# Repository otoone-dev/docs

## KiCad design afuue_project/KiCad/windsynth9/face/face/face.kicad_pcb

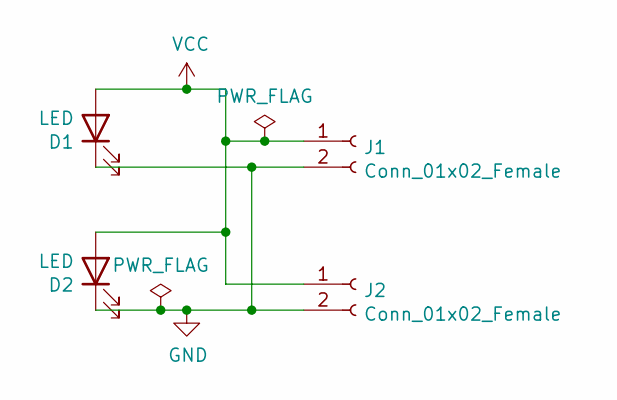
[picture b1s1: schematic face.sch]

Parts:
D1, D2: LED; LED_0603_1608Metric
J1, J2: Conn_01x02_Female; ContactPad_4mm

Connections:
GND: D1.1 (K), D2.1 (K), J1.2, J2.2
VCC: D1.2 (A), D2.2 (A), J1.1, J2.1

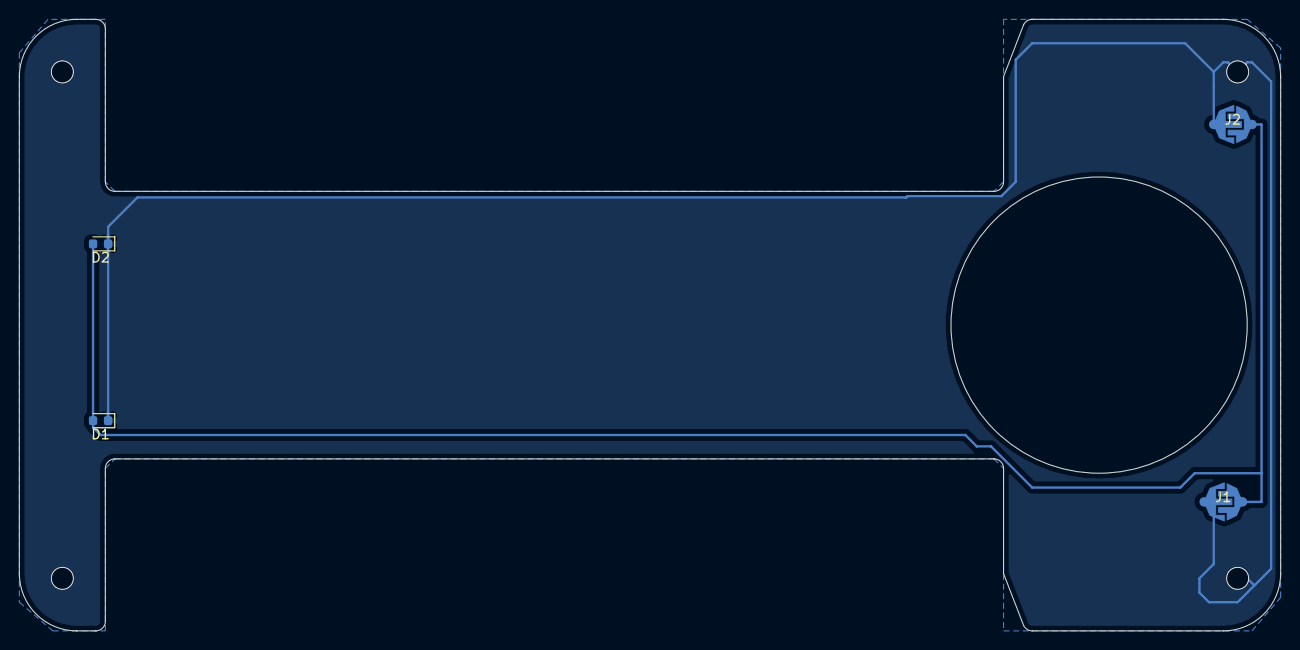
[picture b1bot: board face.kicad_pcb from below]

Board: 2 copper layers, 132.0 x 64.0 mm, 4 parts (4 on the bottom side), 2 nets.

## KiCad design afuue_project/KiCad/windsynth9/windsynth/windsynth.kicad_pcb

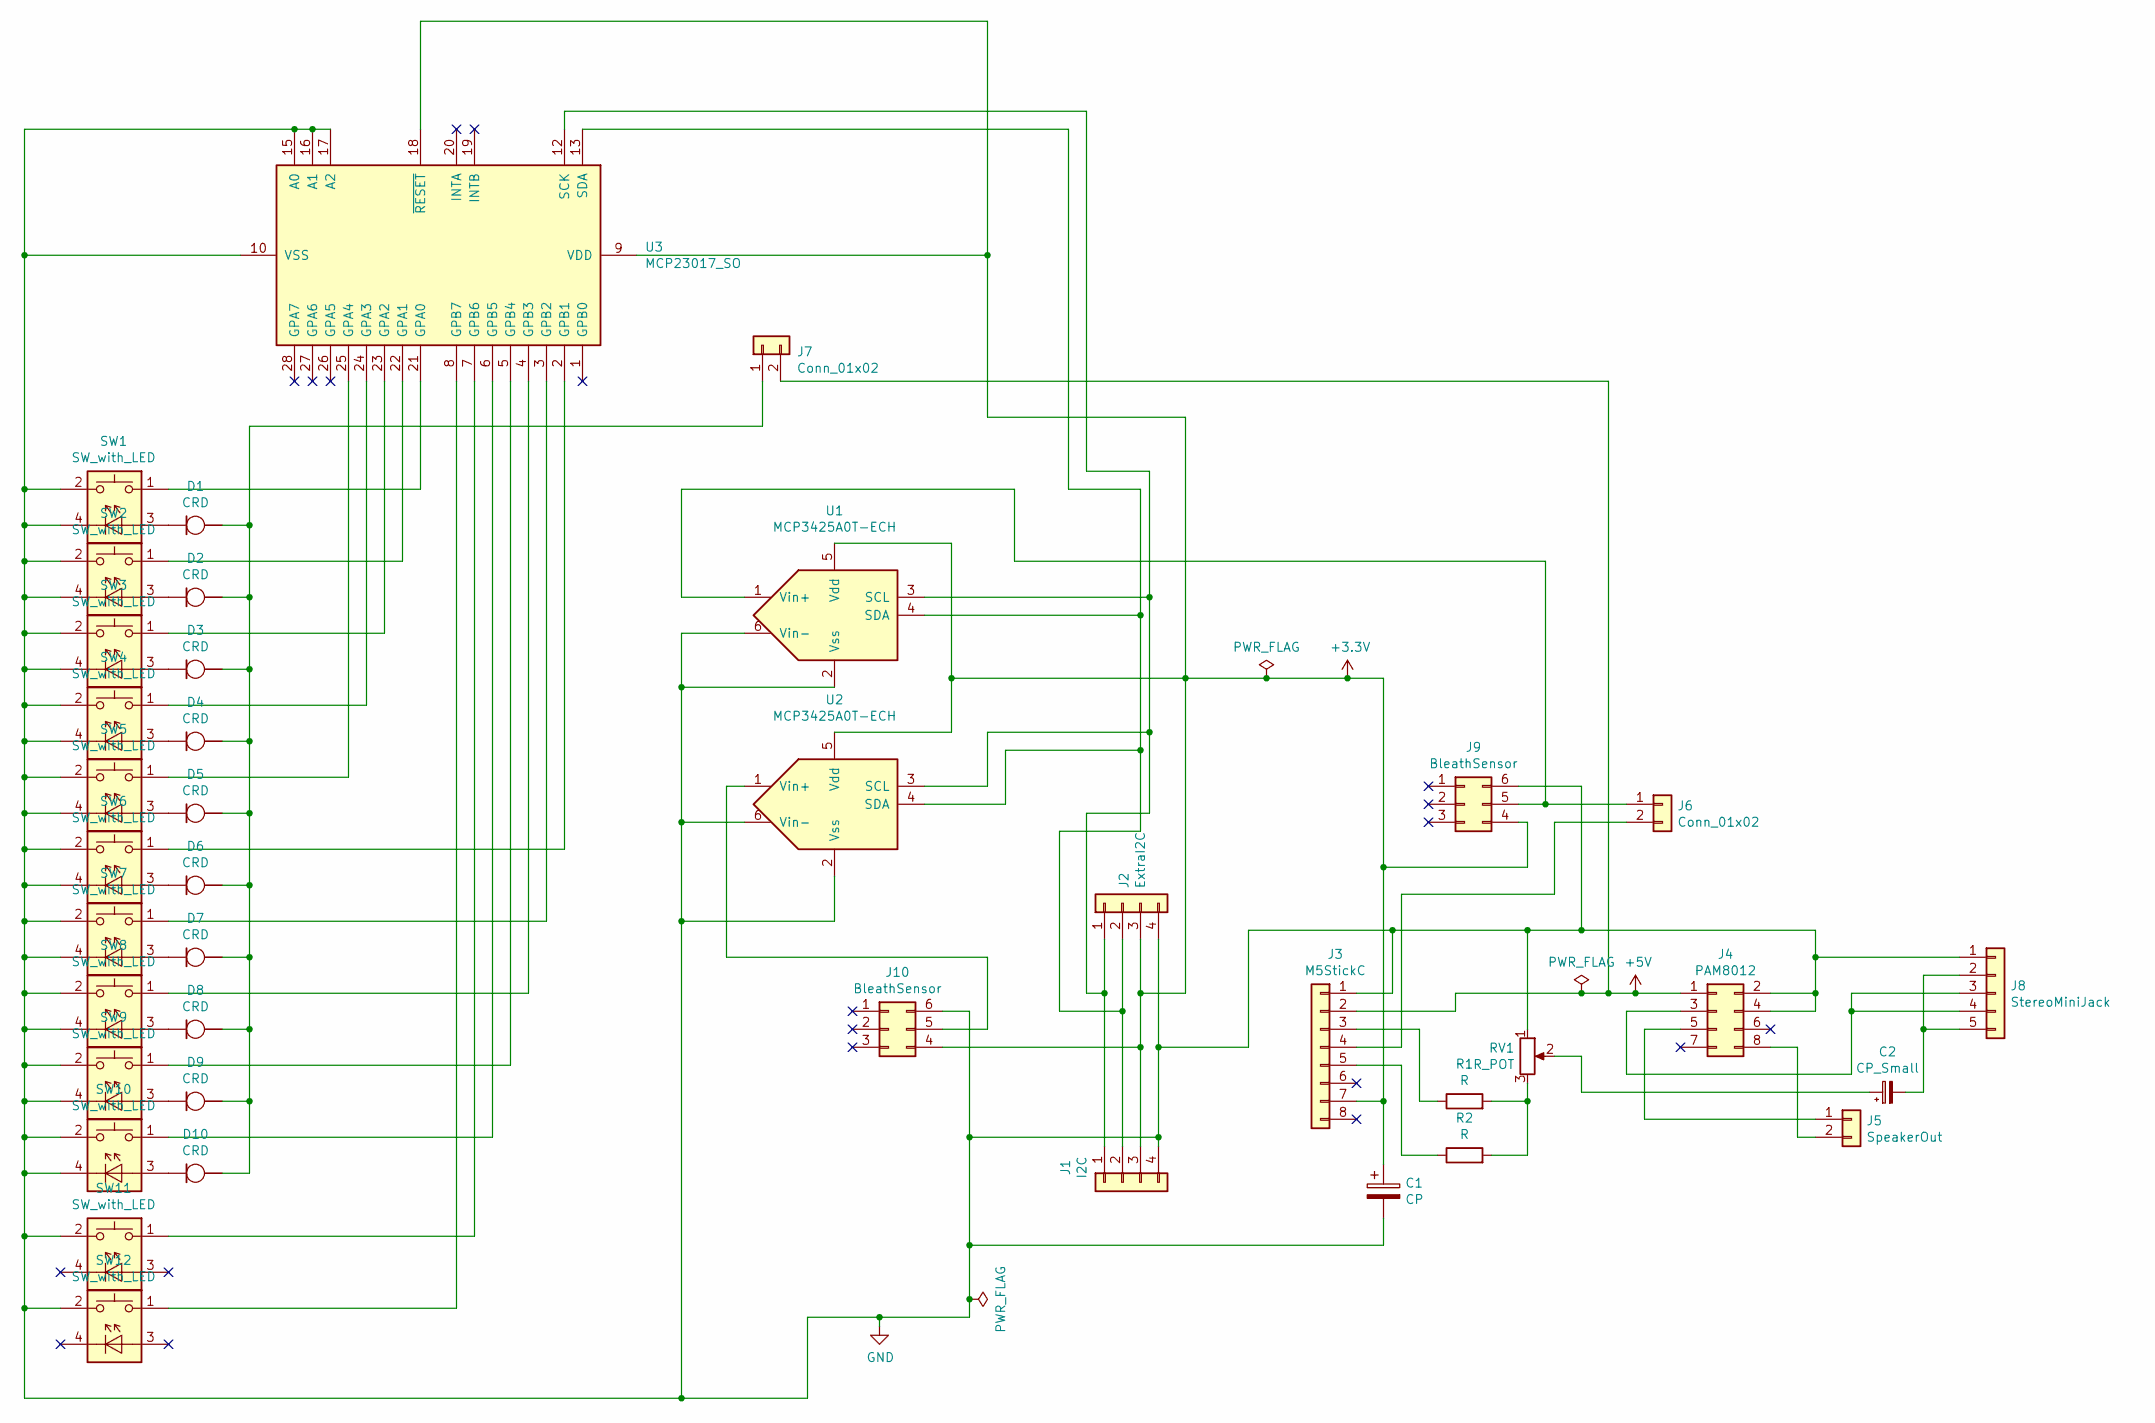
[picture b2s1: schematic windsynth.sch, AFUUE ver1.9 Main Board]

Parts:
C1: CP; PinHeader_1x02_P2.54mm_Vertical
C2: CP_Small; PinHeader_1x02_P2.54mm_Vertical
D1, D2, D3, D4, D5, D6, D7, D8, D9, D10: CRD; LED_0805_2012Metric
J1: I2C; JST_PH_B4B-PH-SM4-TB_1x04-1MP_P2.00mm_Vertical
J2: ExtraI2C; PinHeader_1x04_P2.00mm_Vertical
J3: M5StickC; PinHeader_1x08_P2.54mm_Horizontal
J4: PAM8012; AE-PAM8012
J5: SpeakerOut; USGM30
J6, J7: Conn_01x02; SolderJumper-2_P1.3mm_Open_RoundedPad1.0x1.5mm
J8: StereoMiniJack; PJ-307 AudioJack
J9, J10: BleathSensor; DIP-6_W7.62mm_Reverse
R1, R2: R; PinHeader_1x02_P2.54mm_Vertical
RV1: R_POT; R1001-N16
SW1, SW2, SW3, SW4, SW5, SW6, SW7, SW8, SW9, SW10, SW11, SW12: SW_with_LED; KailhLowProfileSW
U1, U2: MCP3425A0T-ECH; SOT-23-6_Handsoldering
U3: MCP23017_SO; SOIC-28W_7.5x17.9mm_P1.27mm

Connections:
GND: C1.2, J1.4, J2.4, J3.1, J4.2, J4.4, J8.1, J9.6, J10.6, RV1.1, SW1.2, SW1.4, SW2.2, SW2.4, SW3.2, SW3.4, SW4.2, SW4.4, SW5.2, SW5.4, SW6.2, SW6.4, SW7.2, SW7.4, SW8.2, SW8.4, SW9.2, SW9.4, SW10.2, SW10.4, SW11.2, SW12.2, U1.2 (Vss), U1.6 (Vin-), U2.2 (Vss), U2.6 (Vin-), U3.10 (VSS), U3.15 (A0), U3.16 (A1), U3.17 (A2)
unnamed: C2.1, RV1.2
unnamed: C2.2, J8.2, J8.5
unnamed: D1.1 (K), SW1.3
unnamed: D1.2 (A), D2.2 (A), D3.2 (A), D4.2 (A), D5.2 (A), D6.2 (A), D7.2 (A), D8.2 (A), D9.2 (A), D10.2 (A), J7.1
unnamed: D2.1 (K), SW2.3
unnamed: D3.1 (K), SW3.3
unnamed: D4.1 (K), SW4.3
unnamed: D5.1 (K), SW5.3
unnamed: D6.1 (K), SW6.3
unnamed: D7.1 (K), SW7.3
unnamed: D8.1 (K), SW8.3
unnamed: D9.1 (K), SW9.3
unnamed: D10.1 (K), SW10.3
unnamed: J1.1, J2.1, U1.3 (SCL), U2.3 (SCL), U3.12 (SCK)
unnamed: J1.2, J2.2, U1.4 (SDA), U2.4 (SDA), U3.13 (SDA)
unnamed: J3.3, R1.1
unnamed 17: J3.4, J6.2; also elsewhere on the board
unnamed: J3.5, R2.1
unnamed: J4.3, J8.3, J8.4
unnamed: J4.5, J5.1
unnamed: J4.8, J5.2
unnamed 22: J6.1, J9.5, U1.1 (Vin+); also elsewhere on the board
unnamed: J10.5, U2.1 (Vin+)
unnamed: R1.2, R2.2, RV1.3
unnamed: SW1.1, U3.21 (GPA0)
unnamed: SW2.1, U3.22 (GPA1)
unnamed: SW3.1, U3.23 (GPA2)
unnamed: SW4.1, U3.24 (GPA3)
unnamed: SW5.1, U3.25 (GPA4)
unnamed: SW6.1, U3.2 (GPB1)
unnamed: SW7.1, U3.3 (GPB2)
unnamed: SW8.1, U3.4 (GPB3)
unnamed: SW9.1, U3.5 (GPB4)
unnamed: SW10.1, U3.6 (GPB5)
unnamed: SW11.1, U3.7 (GPB6)
unnamed: SW12.1, U3.8 (GPB7)

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
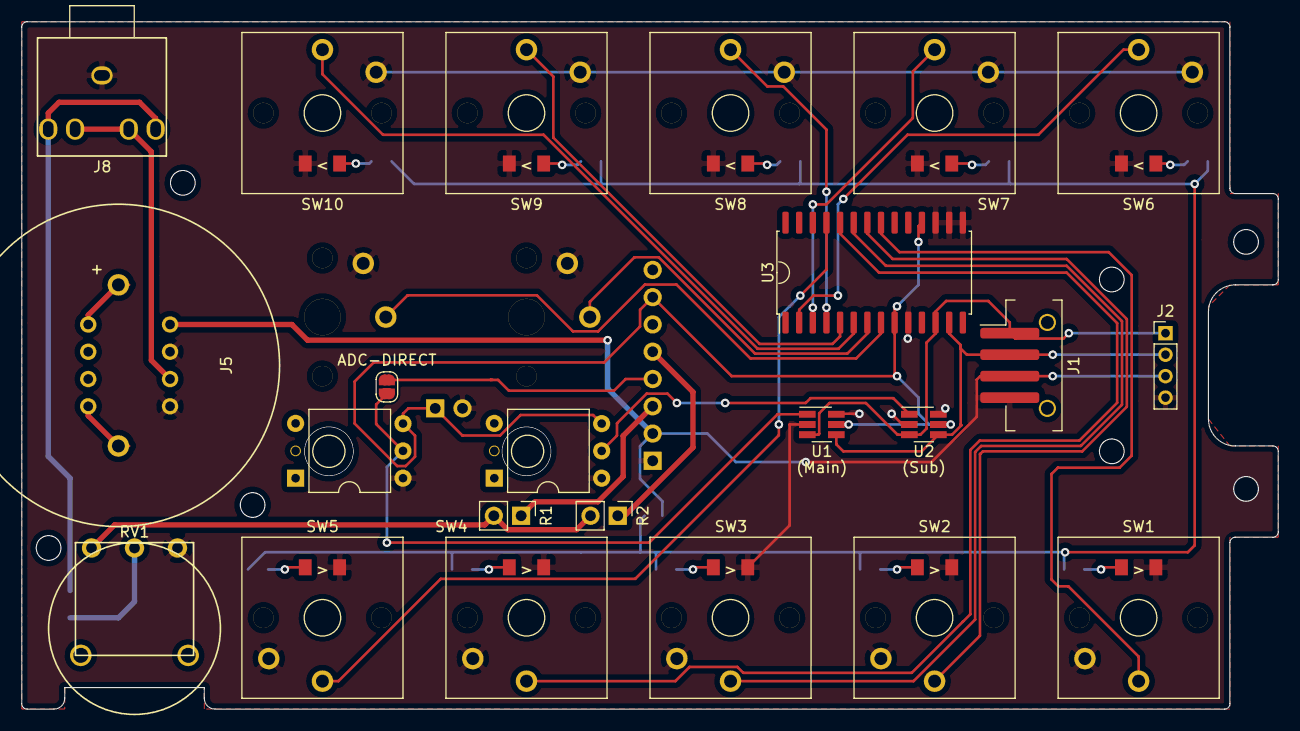
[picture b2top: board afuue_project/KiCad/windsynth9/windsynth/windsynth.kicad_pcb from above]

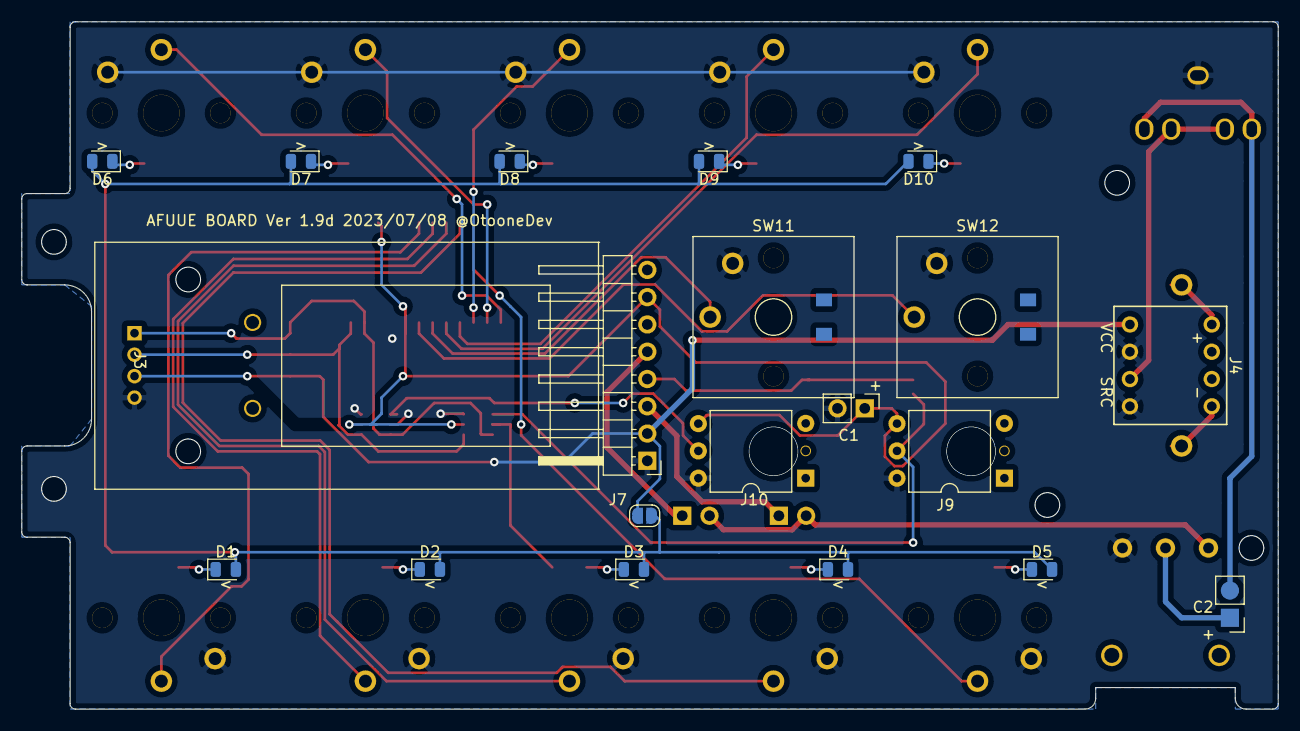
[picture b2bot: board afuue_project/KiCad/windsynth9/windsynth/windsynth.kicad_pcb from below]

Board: 2 copper layers, 117.0 x 64.0 mm, 40 parts (17 on the bottom side), 39 nets.

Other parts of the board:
ADC-DIRECT: Conn_01x02; SolderJumper-2_P1.3mm_Open_RoundedPad1.0x1.5mm

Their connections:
unnamed 17: ADC-DIRECT.2; also elsewhere on the board
unnamed 22: ADC-DIRECT.1; also elsewhere on the board

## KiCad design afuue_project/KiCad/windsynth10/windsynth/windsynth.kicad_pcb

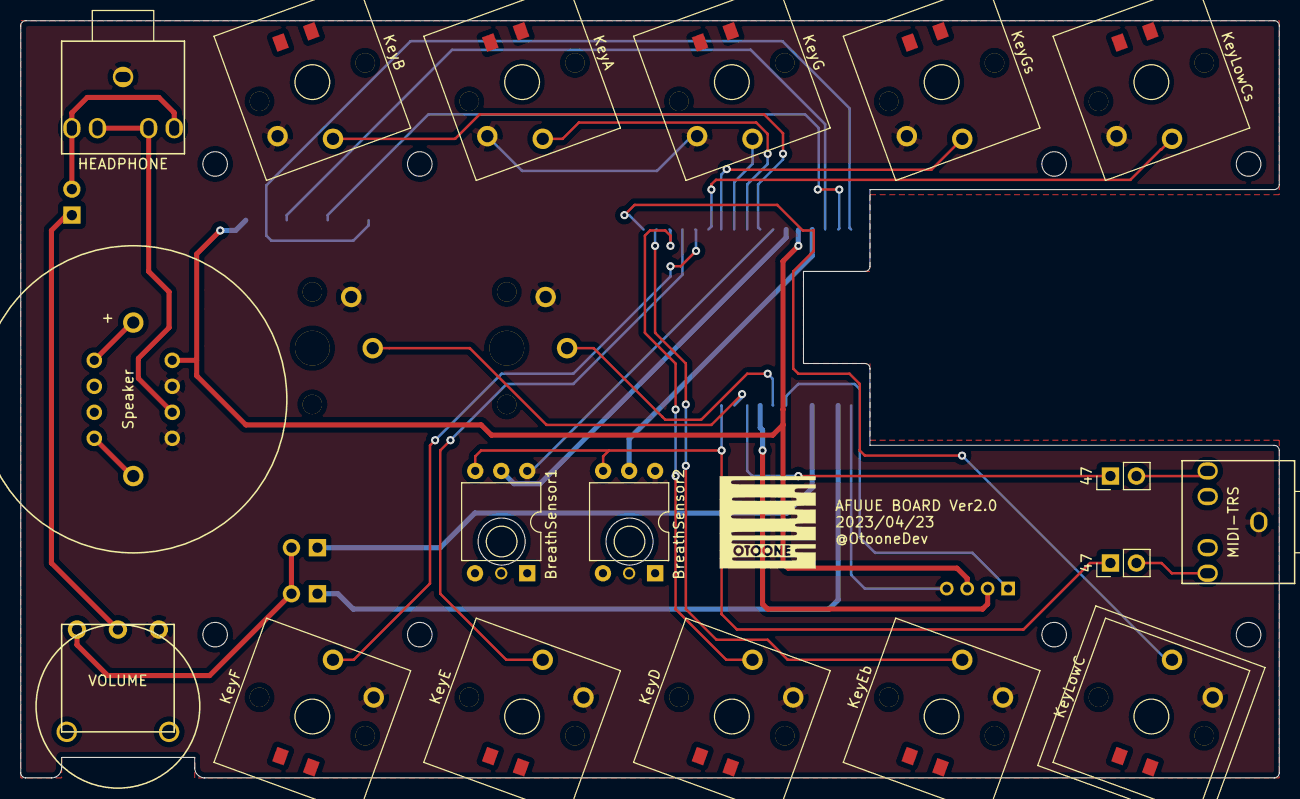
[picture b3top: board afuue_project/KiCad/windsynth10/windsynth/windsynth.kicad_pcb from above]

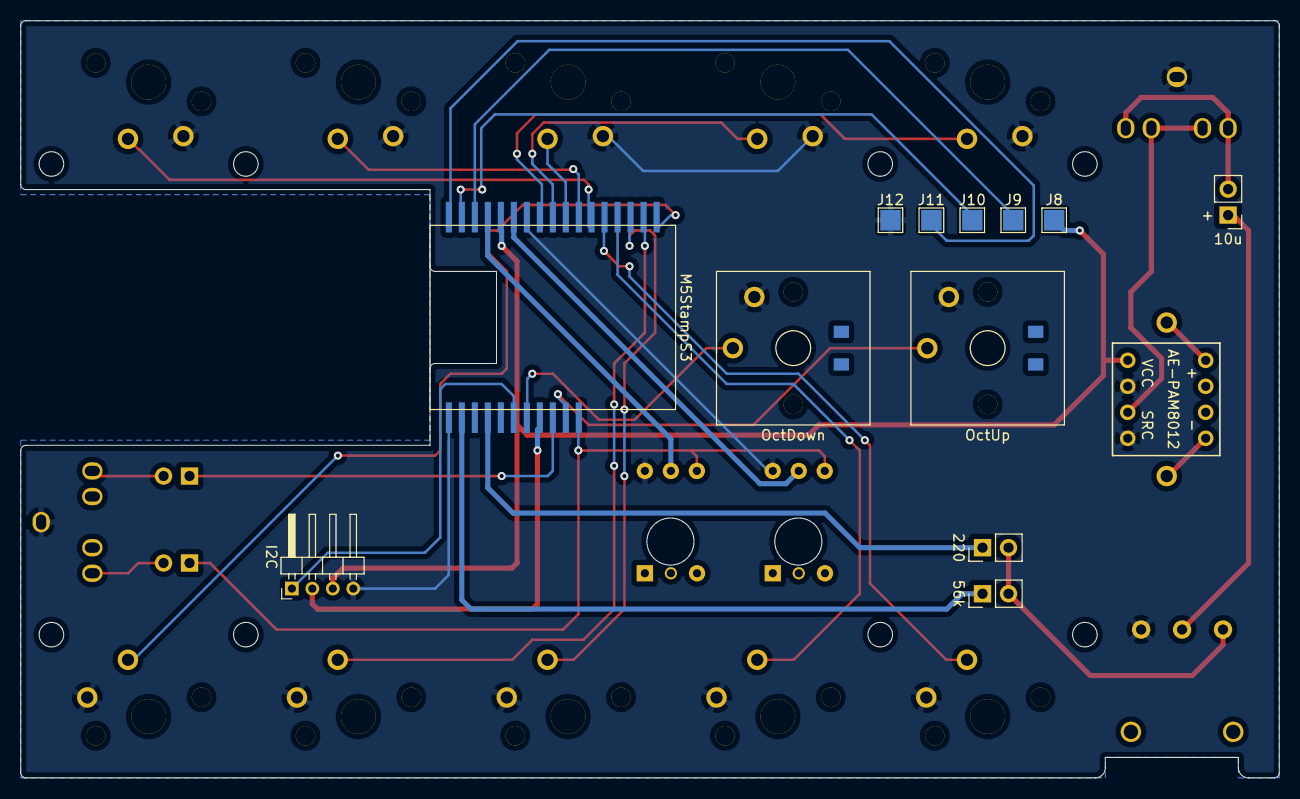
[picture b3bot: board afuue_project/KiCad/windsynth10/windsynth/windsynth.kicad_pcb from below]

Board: 2 copper layers, 123.0 x 74.0 mm, 31 parts (13 on the bottom side), 33 nets.

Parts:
10u: CP1_Small; PinHeader_1x02_P2.54mm_Vertical
47, 47#2: 47; PinHeader_1x02_P2.54mm_Vertical
56k: 56k; PinHeader_1x02_P2.54mm_Vertical
220: 220; PinHeader_1x02_P2.54mm_Vertical
AE-PAM8012: PAM8012; AE-PAM8012
BreathSensor1, BreathSensor2: BleathSensor; DIP-6_W7.62mm_Reverse
HEADPHONE: StereoMiniJack; PJ-307 AudioJack
I2C: I2C; PinHeader_1x04_P2.00mm_Horizontal
J8, J9, J10, J11, J12: Conn_01x01_Male; TestPoint_Pad_2.0x2.0mm
KeyA: SW_with_LED; KailhLowProfileSW
KeyB: SW_with_LED; KailhLowProfileSW
KeyD: SW_with_LED; KailhLowProfileSW
KeyE: SW_with_LED; KailhLowProfileSW
KeyEb: SW_with_LED; KailhLowProfileSW
KeyF: SW_with_LED; KailhLowProfileSW
KeyG: SW_with_LED; KailhLowProfileSW
KeyGs: SW_with_LED; KailhLowProfileSW
KeyLowC: SW_with_LED; KailhLowProfileSW
KeyLowCs: SW_with_LED; KailhLowProfileSW
M5StampS3: M5StampS3
MIDI-TRS: MIDI-TRS; PJ-307 AudioJack
OctDown: SW_with_LED; KailhLowProfileSW
OctUp: SW_with_LED; KailhLowProfileSW
Speaker: SpeakerOut; USGM30
VOLUME: R_POT; R1001-N16

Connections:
+3V3: 47#2.1, BreathSensor1.4, BreathSensor2.4, M5StampS3.28
+5V: AE-PAM8012.1, I2C.3, J8.1, M5StampS3.13
GND: AE-PAM8012.2, AE-PAM8012.4, BreathSensor1.6, BreathSensor2.6, HEADPHONE.1, I2C.4, J12.1, KeyA.2, KeyB.2, KeyD.2, KeyE.2, KeyEb.2, KeyF.2, KeyG.2, KeyGs.2, KeyLowC.2, KeyLowCs.2, M5StampS3.11, M5StampS3.18, MIDI-TRS.1, OctDown.2, OctUp.2, VOLUME.1
unnamed: 10u.1, VOLUME.2
unnamed: 10u.2, HEADPHONE.2, HEADPHONE.5
unnamed: BreathSensor1.5, M5StampS3.12
unnamed: BreathSensor2.5, M5StampS3.14
unnamed: AE-PAM8012.3, HEADPHONE.3, HEADPHONE.4
unnamed: 47.2, MIDI-TRS.2
unnamed: 47#2.2, MIDI-TRS.5
unnamed: AE-PAM8012.5, Speaker.1
unnamed: AE-PAM8012.8, Speaker.2
unnamed: I2C.1, M5StampS3.23
unnamed: I2C.2, M5StampS3.25
unnamed: J9.1, M5StampS3.15
unnamed: J10.1, M5StampS3.16
unnamed: J11.1, M5StampS3.17
unnamed: KeyA.1, M5StampS3.9
unnamed: KeyB.1, M5StampS3.10
unnamed: KeyD.1, M5StampS3.3
unnamed: KeyEb.1, M5StampS3.2
unnamed: KeyE.1, M5StampS3.4
unnamed: KeyF.1, M5StampS3.5
unnamed: KeyG.1, M5StampS3.8
unnamed: KeyGs.1, M5StampS3.7
unnamed: KeyLowC.1, M5StampS3.1
unnamed: KeyLowCs.1, M5StampS3.6
unnamed: M5StampS3.24, OctDown.1
unnamed: M5StampS3.27, OctUp.1
unnamed: 56k.1, M5StampS3.19
unnamed: 56k.2, 220.2, VOLUME.3
unnamed: 220.1, M5StampS3.21
unnamed: 47.1, M5StampS3.26

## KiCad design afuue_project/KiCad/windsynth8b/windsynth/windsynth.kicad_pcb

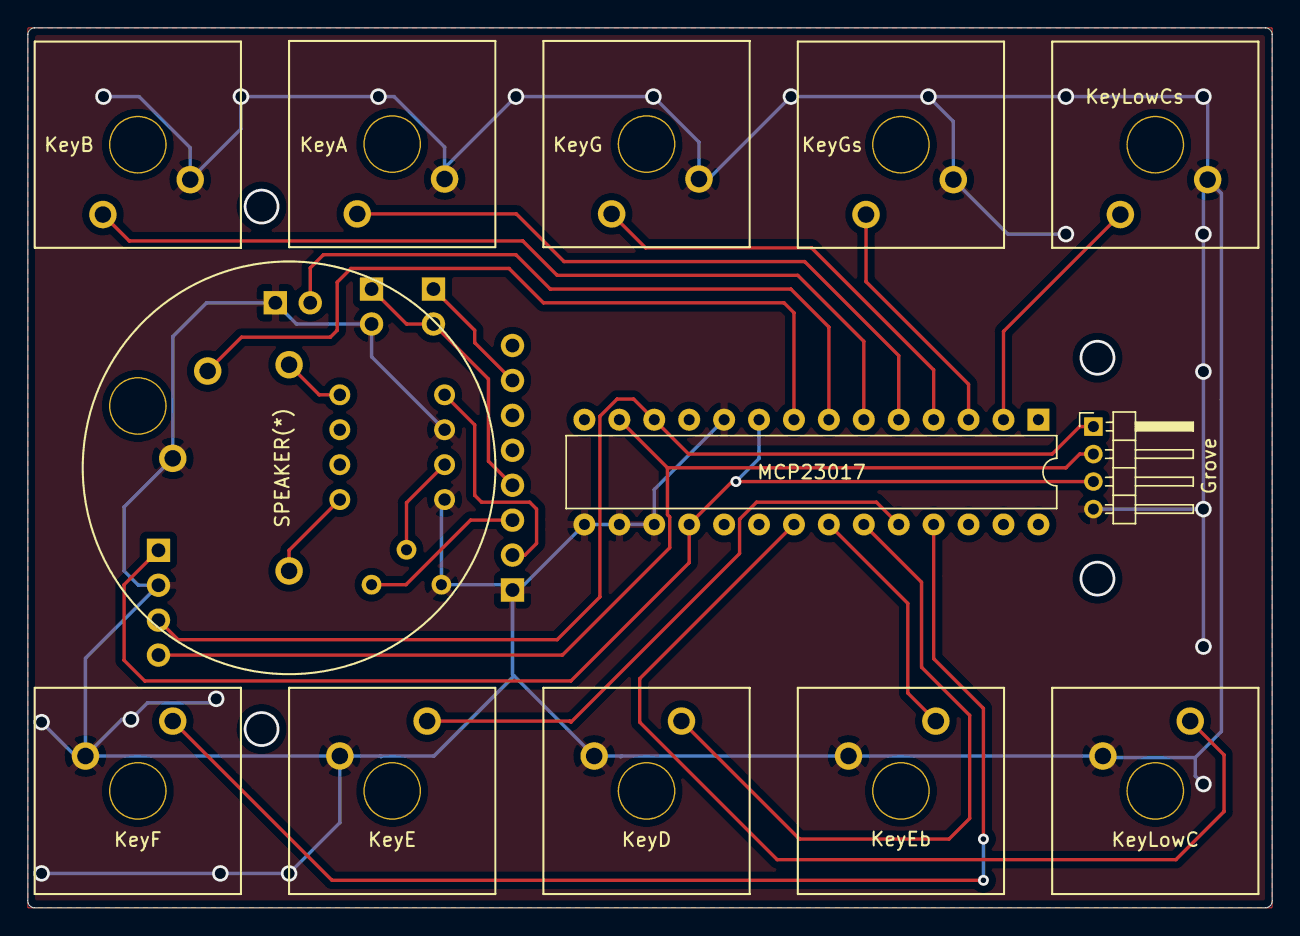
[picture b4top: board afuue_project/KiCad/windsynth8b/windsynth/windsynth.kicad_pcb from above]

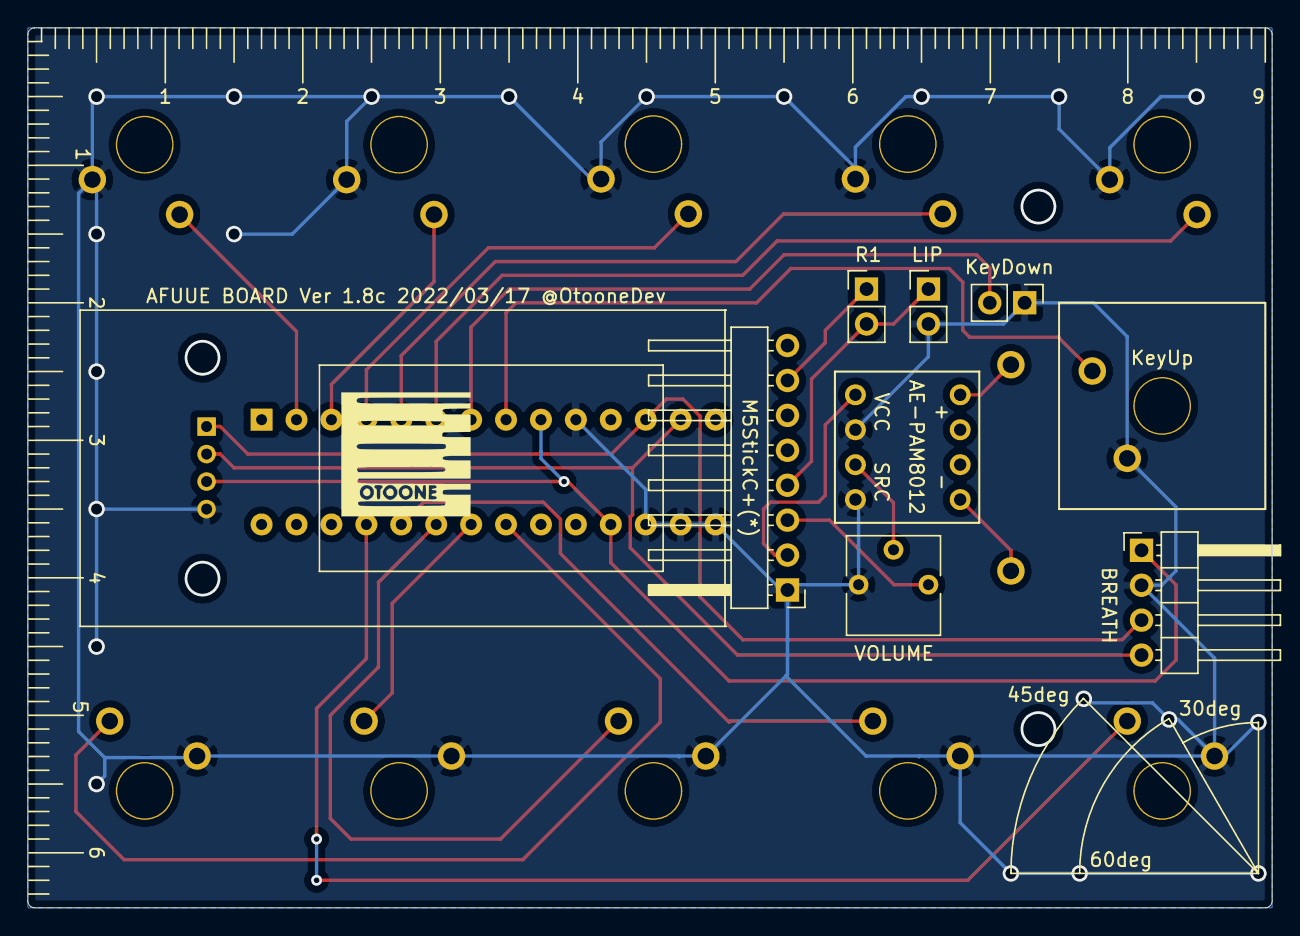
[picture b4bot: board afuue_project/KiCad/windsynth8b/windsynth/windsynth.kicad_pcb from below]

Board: 2 copper layers, 90.5 x 64.0 mm, 21 parts (8 on the bottom side), 23 nets.

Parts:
AE-PAM8012: Conn_02x04_Odd_Even; AE-PAM8012
BREATH: Conn_01x04; PinHeader_1x04_P2.54mm_Horizontal
Grove: Conn_01x04; PinHeader_1x04_P2.00mm_Horizontal
KeyA: SW_Push; CherryMX-Switch
KeyB: SW_Push; CherryMX-Switch
KeyD: SW_Push; CherryMX-Switch
KeyDown: SW_Push; PinHeader_1x02_P2.54mm_Vertical
KeyE: SW_Push; CherryMX-Switch
KeyEb: SW_Push; CherryMX-Switch
KeyF: SW_Push; CherryMX-Switch
KeyG: SW_Push; CherryMX-Switch
KeyGs: SW_Push; CherryMX-Switch
KeyLowC: SW_Push; CherryMX-Switch
KeyLowCs: SW_Push; CherryMX-Switch
KeyUp: SW_Push; CherryMX-Switch
LIP: Conn_01x02; PinHeader_1x02_P2.54mm_Vertical
M5StickC+(*): Conn_01x08; PinHeader_1x08_P2.54mm_Horizontal
MCP23017: MCP23017_SP; DIP-28_W7.62mm
R1: R; PinHeader_1x02_P2.54mm_Vertical
SPEAKER(*): Conn_01x02; USGM30
VOLUME: R_POT; Potentiometer_Vishay_T73YP_Vertical

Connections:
+5V: BREATH.1, Grove.3, MCP23017.9, MCP23017.18
GND: AE-PAM8012.2, AE-PAM8012.4, BREATH.2, Grove.4, KeyA.1, KeyB.1, KeyD.1, KeyDown.1, KeyE.1, KeyEb.1, KeyF.1, KeyG.1, KeyGs.1, KeyLowC.1, KeyLowCs.1, KeyUp.1, LIP.2, M5StickC+(*).1, MCP23017.10, MCP23017.15, MCP23017.16, MCP23017.17, VOLUME.3
unnamed: BREATH.3, Grove.1, MCP23017.12
unnamed: BREATH.4, Grove.2, MCP23017.13
unnamed: AE-PAM8012.1, M5StickC+(*).2
unnamed: M5StickC+(*).3, VOLUME.1
unnamed: LIP.1, M5StickC+(*).4, R1.2
unnamed: M5StickC+(*).7, R1.1
unnamed: AE-PAM8012.3, VOLUME.2
unnamed: AE-PAM8012.5, SPEAKER(*).1
unnamed: AE-PAM8012.8, SPEAKER(*).2
unnamed: KeyLowC.2, MCP23017.21
unnamed: KeyEb.2, MCP23017.22
unnamed: KeyD.2, MCP23017.23
unnamed: KeyE.2, MCP23017.24
unnamed: KeyF.2, MCP23017.25
unnamed: KeyLowCs.2, MCP23017.2
unnamed: KeyGs.2, MCP23017.3
unnamed: KeyG.2, MCP23017.4
unnamed: KeyA.2, MCP23017.5
unnamed: KeyB.2, MCP23017.6
unnamed: KeyDown.2, MCP23017.7
unnamed: KeyUp.2, MCP23017.8

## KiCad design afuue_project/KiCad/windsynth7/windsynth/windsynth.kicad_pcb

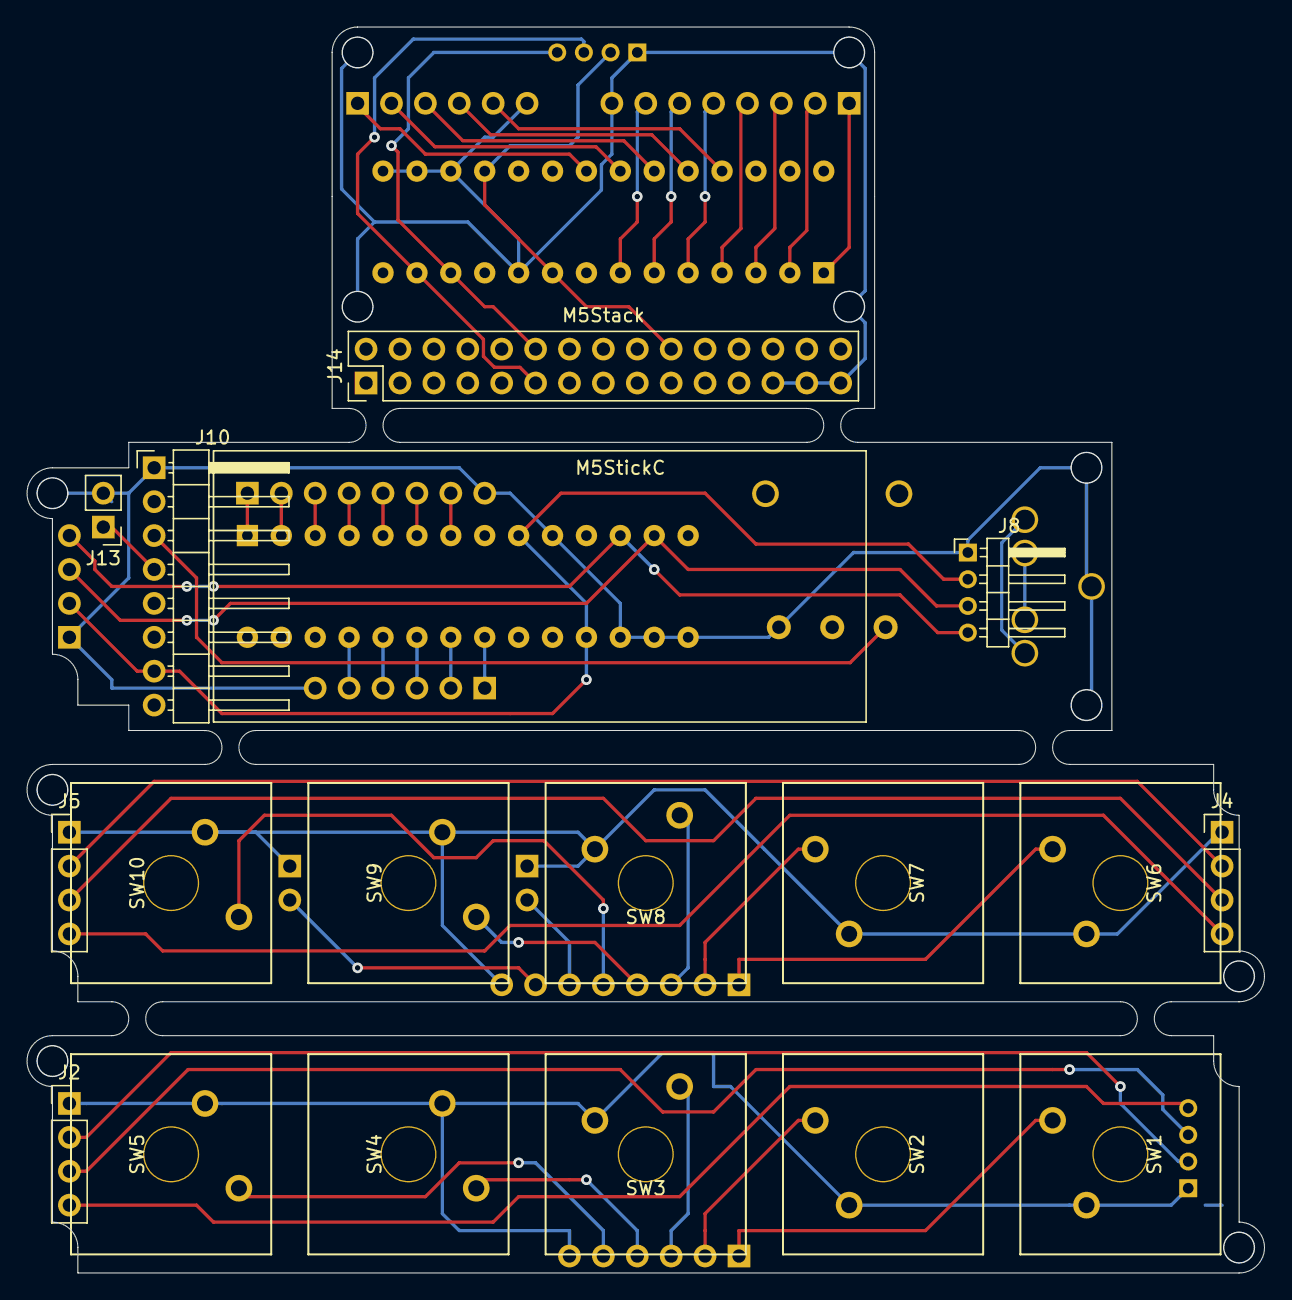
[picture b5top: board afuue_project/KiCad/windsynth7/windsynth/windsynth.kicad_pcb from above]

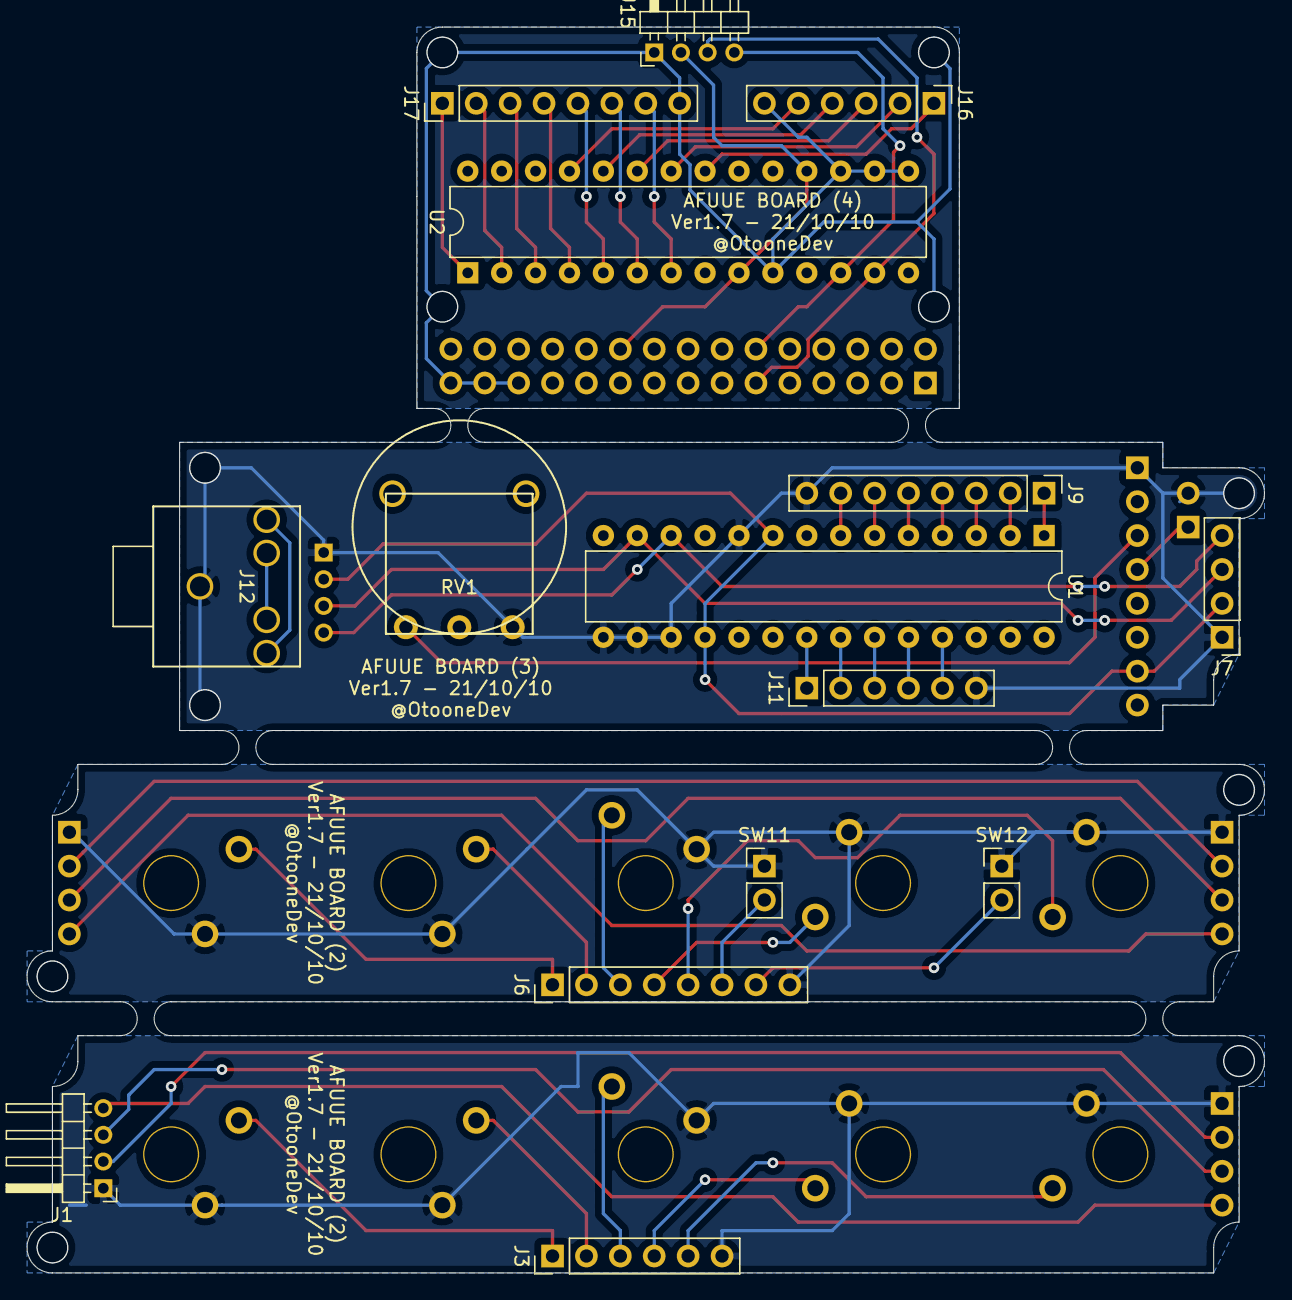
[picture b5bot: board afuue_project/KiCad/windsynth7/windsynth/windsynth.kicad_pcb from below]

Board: 2 copper layers, 92.7 x 93.3 mm, 32 parts (15 on the bottom side), 56 nets.

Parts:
J1, J8, J15: Conn_01x04; PinHeader_1x04_P2.00mm_Horizontal
J2, J4, J5, J7: Conn_01x04; PinHeader_1x04_P2.54mm_Vertical
J3, J11, J16: Conn_01x06; PinHeader_1x06_P2.54mm_Vertical
J6, J9, J17: Conn_01x08; PinHeader_1x08_P2.54mm_Vertical
J10: Conn_01x08; PinHeader_1x08_P2.54mm_Horizontal
J12: Conn_01x05; PJ-307 AudioJack
J13: Conn_01x02; PinHeader_1x02_P2.54mm_Vertical
J14: Conn_02x15_Odd_Even; PinHeader_2x15_P2.54mm_Vertical
RV1: R_POT; R1001-N16
SW1, SW2, SW3, SW4, SW5, SW6, SW7, SW8, SW9, SW10: SW_Push; CherryMX-Switch
SW11, SW12: SW_Push; PinHeader_1x02_P2.54mm_Vertical
U1, U2: MCP23S17_SP; DIP-28_W7.62mm

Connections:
+3V3: J7.2, J8.2, J10.7, U1.9, U1.18
GND: J1.1, J2.1, J3.6, SW1.1, SW2.1, SW3.1, SW4.1, SW5.1
GND1: J4.1, J5.1, J6.8, SW6.1, SW7.1, SW8.1, SW9.1, SW10.1, SW11.1, SW12.1
GND2: J7.1, J8.1, J9.8, J10.1, J11.6, J12.1, J13.2, RV1.3, U1.10, U1.15, U1.16, U1.17
GND3: J14.25, J14.27, J14.29, J15.1, J16.6, J17.8, U2.10, U2.15, U2.16, U2.17
unnamed: J1.2, J2.2
unnamed: J1.3, J2.3
unnamed: J1.4, J2.4
unnamed: J3.1, SW1.2
unnamed: J3.2, SW2.2
unnamed: J3.3, SW3.2
unnamed: J3.4, SW4.2
unnamed: J3.5, SW5.2
unnamed: J4.2, J5.2
unnamed: J4.3, J5.3
unnamed: J4.4, J5.4
unnamed: J6.1, SW6.2
unnamed: J6.2, SW7.2
unnamed: J6.3, SW8.2
unnamed: J6.4, SW9.2
unnamed: J6.5, SW10.2
unnamed: J6.6, SW11.2
unnamed: J6.7, SW12.2
unnamed: J7.3, J8.3, U1.13
unnamed: J7.4, J8.4, U1.12
unnamed: J9.1, U1.1
unnamed: J9.2, U1.2
unnamed: J9.3, U1.3
unnamed: J9.4, U1.4
unnamed: J9.5, U1.5
unnamed: J9.6, U1.6
unnamed: J9.7, U1.7
unnamed: J10.3, RV1.1
unnamed: J10.4, J13.1
unnamed: J11.1, U1.21
unnamed: J11.2, U1.22
unnamed: J11.3, U1.23
unnamed: J11.4, U1.24
unnamed: J11.5, U1.25
unnamed: J12.2, J12.5, RV1.2
unnamed: J12.3, J12.4
unnamed: J14.11, J15.3, U2.13
unnamed: J14.12, J15.4, U2.12
unnamed: J14.20, J15.2, U2.9, U2.18
unnamed: J16.1, U2.21
unnamed: J16.2, U2.22
unnamed: J16.3, U2.23
unnamed: J16.4, U2.24
unnamed: J16.5, U2.25
unnamed: J17.1, U2.1
unnamed: J17.2, U2.2
unnamed: J17.3, U2.3
unnamed: J17.4, U2.4
unnamed: J17.5, U2.5
unnamed: J17.6, U2.6
unnamed: J17.7, U2.7
